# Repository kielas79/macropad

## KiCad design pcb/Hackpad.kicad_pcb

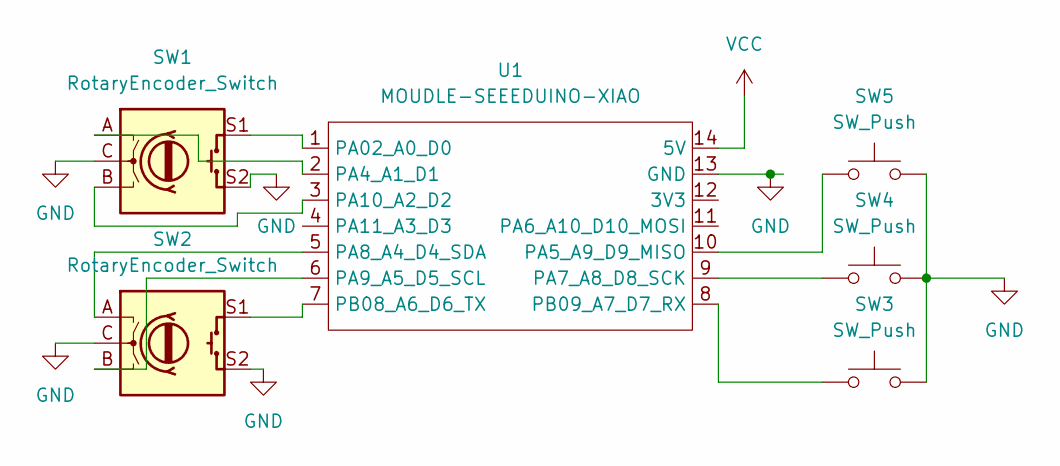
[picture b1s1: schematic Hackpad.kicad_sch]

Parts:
SW1, SW2: RotaryEncoder_Switch; RotaryEncoder_Alps_EC11E-Switch_Vertical_H20mm
SW3, SW4, SW5: SW_Push; SW_Cherry_MX_1.00u_PCB
U1: MOUDLE-SEEEDUINO-XIAO; XIAO-Generic-Hybrid-14P-2.54-21X17.8MM

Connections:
GND: SW1.C, SW1.S2, SW2.C, SW2.S2, SW3.2, SW4.2, SW5.2, U1.13 (GND)
unnamed: SW1.S1, U1.1 (PA02_A0_D0)
unnamed: SW1.A, U1.2 (PA4_A1_D1)
unnamed: SW5.1, U1.10 (PA5_A9_D9_MISO)
unnamed: SW4.1, U1.9 (PA7_A8_D8_SCK)
unnamed: SW2.A, U1.5 (PA8_A4_D4_SDA)
unnamed: SW2.B, U1.6 (PA9_A5_D5_SCL)
unnamed: SW1.B, U1.3 (PA10_A2_D2)
unnamed: SW2.S1, U1.7 (PB08_A6_D6_TX)
unnamed: SW3.1, U1.8 (PB09_A7_D7_RX)
VCC: U1.14 (5V)

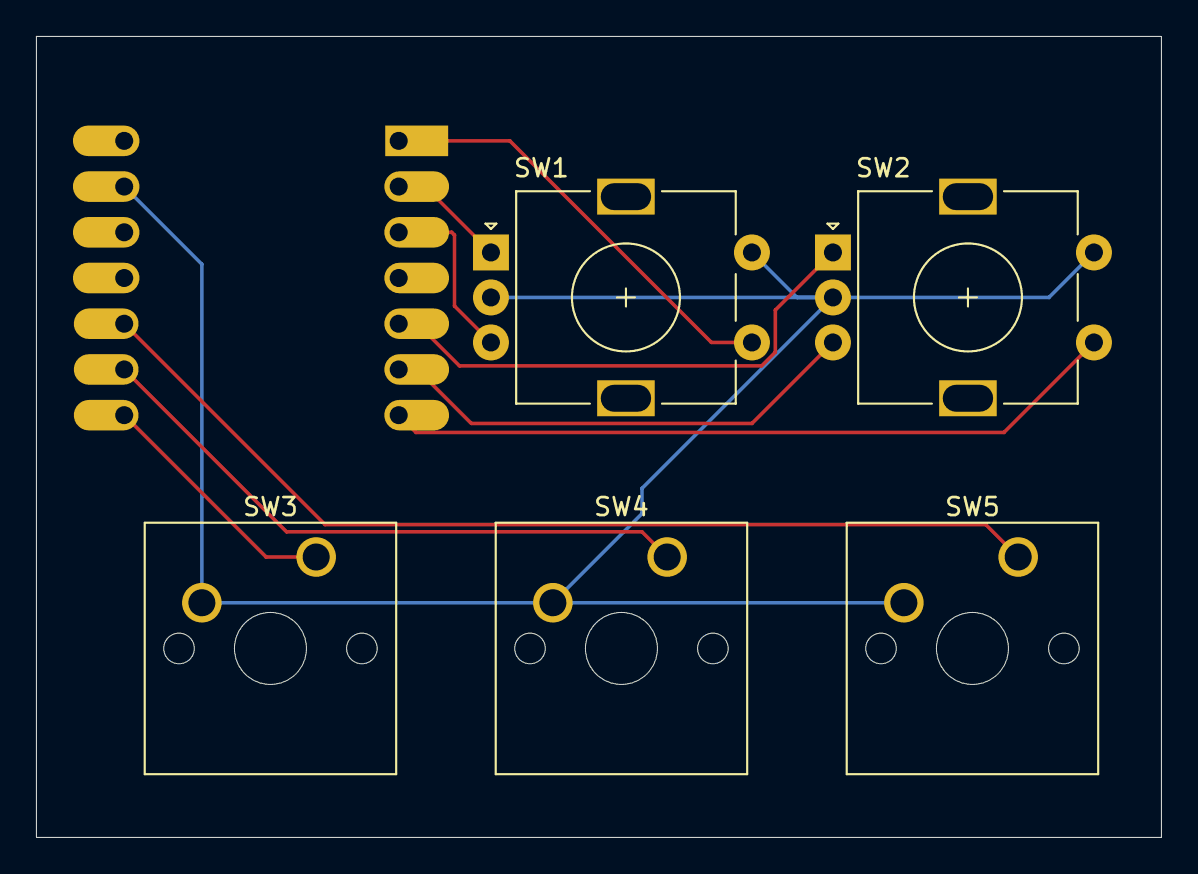
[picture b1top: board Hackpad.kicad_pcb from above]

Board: 2 copper layers, 62.5 x 44.5 mm, 6 parts (1 on the bottom side), 10 nets.
